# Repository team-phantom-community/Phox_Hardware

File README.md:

# Phoxハードウェア

## 概要
Phoxのハードウェアは完全自作のマイコンボードを中核として様々な小型デバイスを用いている

特にここでは
- 自作ボード回路図
- ハードウェアコンポーネント
- ハードウェア用C++コード

について述べていく

## 必須環境
- Kicad Version 7
- Arduino IDE 2
- ソルダーペースト（ペースト半田）
  - 必須ではないが推奨される
- 半田ごて
- ホットプレート or 温度制限機能付きコンロとフライパン
- 3Dプリンター
- 根気<-最重要

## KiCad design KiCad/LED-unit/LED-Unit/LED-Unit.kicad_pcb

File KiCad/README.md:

# KiCadデータ

## 回路

### メインボード
- CPU : ESP32S3
- Battery : 3.7V 400mAh

- PhoxのメインボードにはESP32S3を用いている
  - ESP32S3は、ビルドインのUSBシリアル変換を用いることでプログラム可能な構成としている
  - なお、書き込みデバイスについてであるが、私の環境ではUSB-Cの半田付けが上手くできなかったため、一般的なUSBケーブルを切って、XHを打ったものを用いている
- カメラモジュールの部分は[ESP32-S3 EYE MB_V2.2](https://dl.espressif.com/dl/schematics/SCH_ESP32-S3-EYE-MB_20211201_V2.2.pdf)を参考に作成してある
- カメラはOV5640を用いる想定になっている
  - OV5640は、OV2640と違いDC1.2Vを必要としないため、個人でESPカメラを自作する際には回路設計の負担が減り、おすすめである
  - OV5640のモジュールは国内であればAmazon、国外であればAliExpressで沢山見つけることができる
- このメインボードでは、実装面積をできるだけ小さくするために4層基板を用いている
- 基板製造はJLCPCBにて行った
  - 個人的にはJLCPCBで作成した基板でパターンがつながっていなかったりしたことがないのでJLCPCBはおすすめである
  - 4層基板であっても5枚で$7(日本円で1,100円)程度製造可能である
- また、部品点数およびサイズが小さかったためリフロー半田付けを行った
  - この際にステンシルがあるとソルダーペーストを載せる時間を大幅に短縮できとても良い
    - が、ステンシルはそれなりに高価なのでお金と時間を考えて相対効果の高いほうを選ぶのが得策だろう
  - リフローの方法についてはGoogleで探せばいろいろ見つかるだろうし、あまり私がやっている方法は推奨されないのでここには記さないこととする
- 完成した基板にUSBをつなげて、Arduino IDE上でCOMポートが認識されていれば問題なし
- IDEでボードの種類をeps32->「ESP32S3 Dev Module」で選択し、[CameraServer](CameraWebServer_Phox_version)を書き込んでシリアルモニタに表示されたhttpアドレスにアクセスし、「Start Stream」をクリックして、カメラの画像が表示されれば基板完成となる

### ドアスイッチモジュール
- PhoxのMBのスイッチング用の磁気スイッチと測距センサを備えたモジュール
- 磁気スイッチにはALPSALPINE社のHGDEST021Bを用いている
  - このMEMSデバイスはALPSALPINE社から直接ご提供いただいた
- 測距センサにはSTMicro社のVL53L0xを用いている
  - このVL53L0xは電源電圧がOV5640と同じ2.8Vであり、非常に使いやすい
- Drawingを見てもらえば分かると思うが、このモジュールはドア近くに付けるという特性上、小型であることが求められるため、幅に関してはPH6ピンコネクタベースと同程度となっている

### LEDユニット
- 郵便受け内が暗くなりがちであることから適切に画像認識を行うためにPhoxにはLEDユニットが搭載されている
- この回路はLEDを並列につなげたものであるため、詳しい説明は省かせていただく

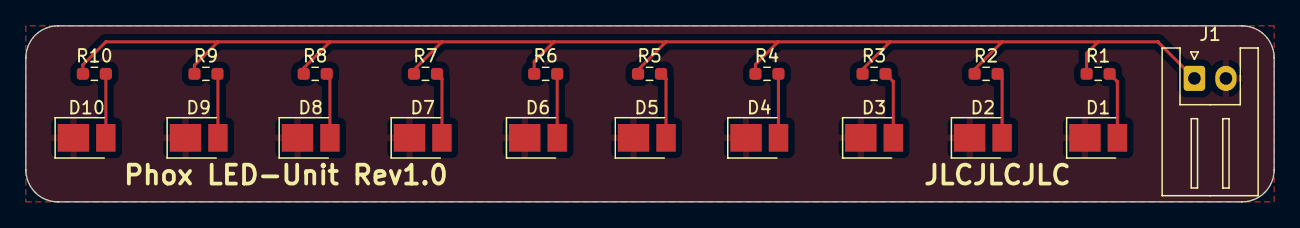
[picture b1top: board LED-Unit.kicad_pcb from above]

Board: 2 copper layers, 99.1 x 14.0 mm, 21 parts (0 on the bottom side), 12 nets.

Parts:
D1, D2, D3, D4, D5, D6, D7, D8, D9, D10: TX1812DXA-F01; LED_PLCC_2835_Handsoldering
J1: Conn_01x02_Socket; JST_XH_S2B-XH-A_1x02_P2.50mm_Horizontal
R1, R2, R3, R4, R5, R6, R7, R8, R9, R10: 100R; R_0603_1608Metric_Pad0.98x0.95mm_HandSolder

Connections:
/GND: D1.1 (K), D2.1 (K), D3.1 (K), D4.1 (K), D5.1 (K), D6.1 (K), D7.1 (K), D8.1 (K), D9.1 (K), D10.1 (K), J1.2
unnamed: D1.2 (A), R1.2
unnamed: D2.2 (A), R2.2
unnamed: D3.2 (A), R3.2
unnamed: D4.2 (A), R4.2
unnamed: D5.2 (A), R5.2
unnamed: D6.2 (A), R6.2
unnamed: D7.2 (A), R7.2
unnamed: D8.2 (A), R8.2
unnamed: D9.2 (A), R9.2
unnamed: D10.2 (A), R10.2
unnamed: J1.1, R1.1, R2.1, R3.1, R4.1, R5.1, R6.1, R7.1, R8.1, R9.1, R10.1

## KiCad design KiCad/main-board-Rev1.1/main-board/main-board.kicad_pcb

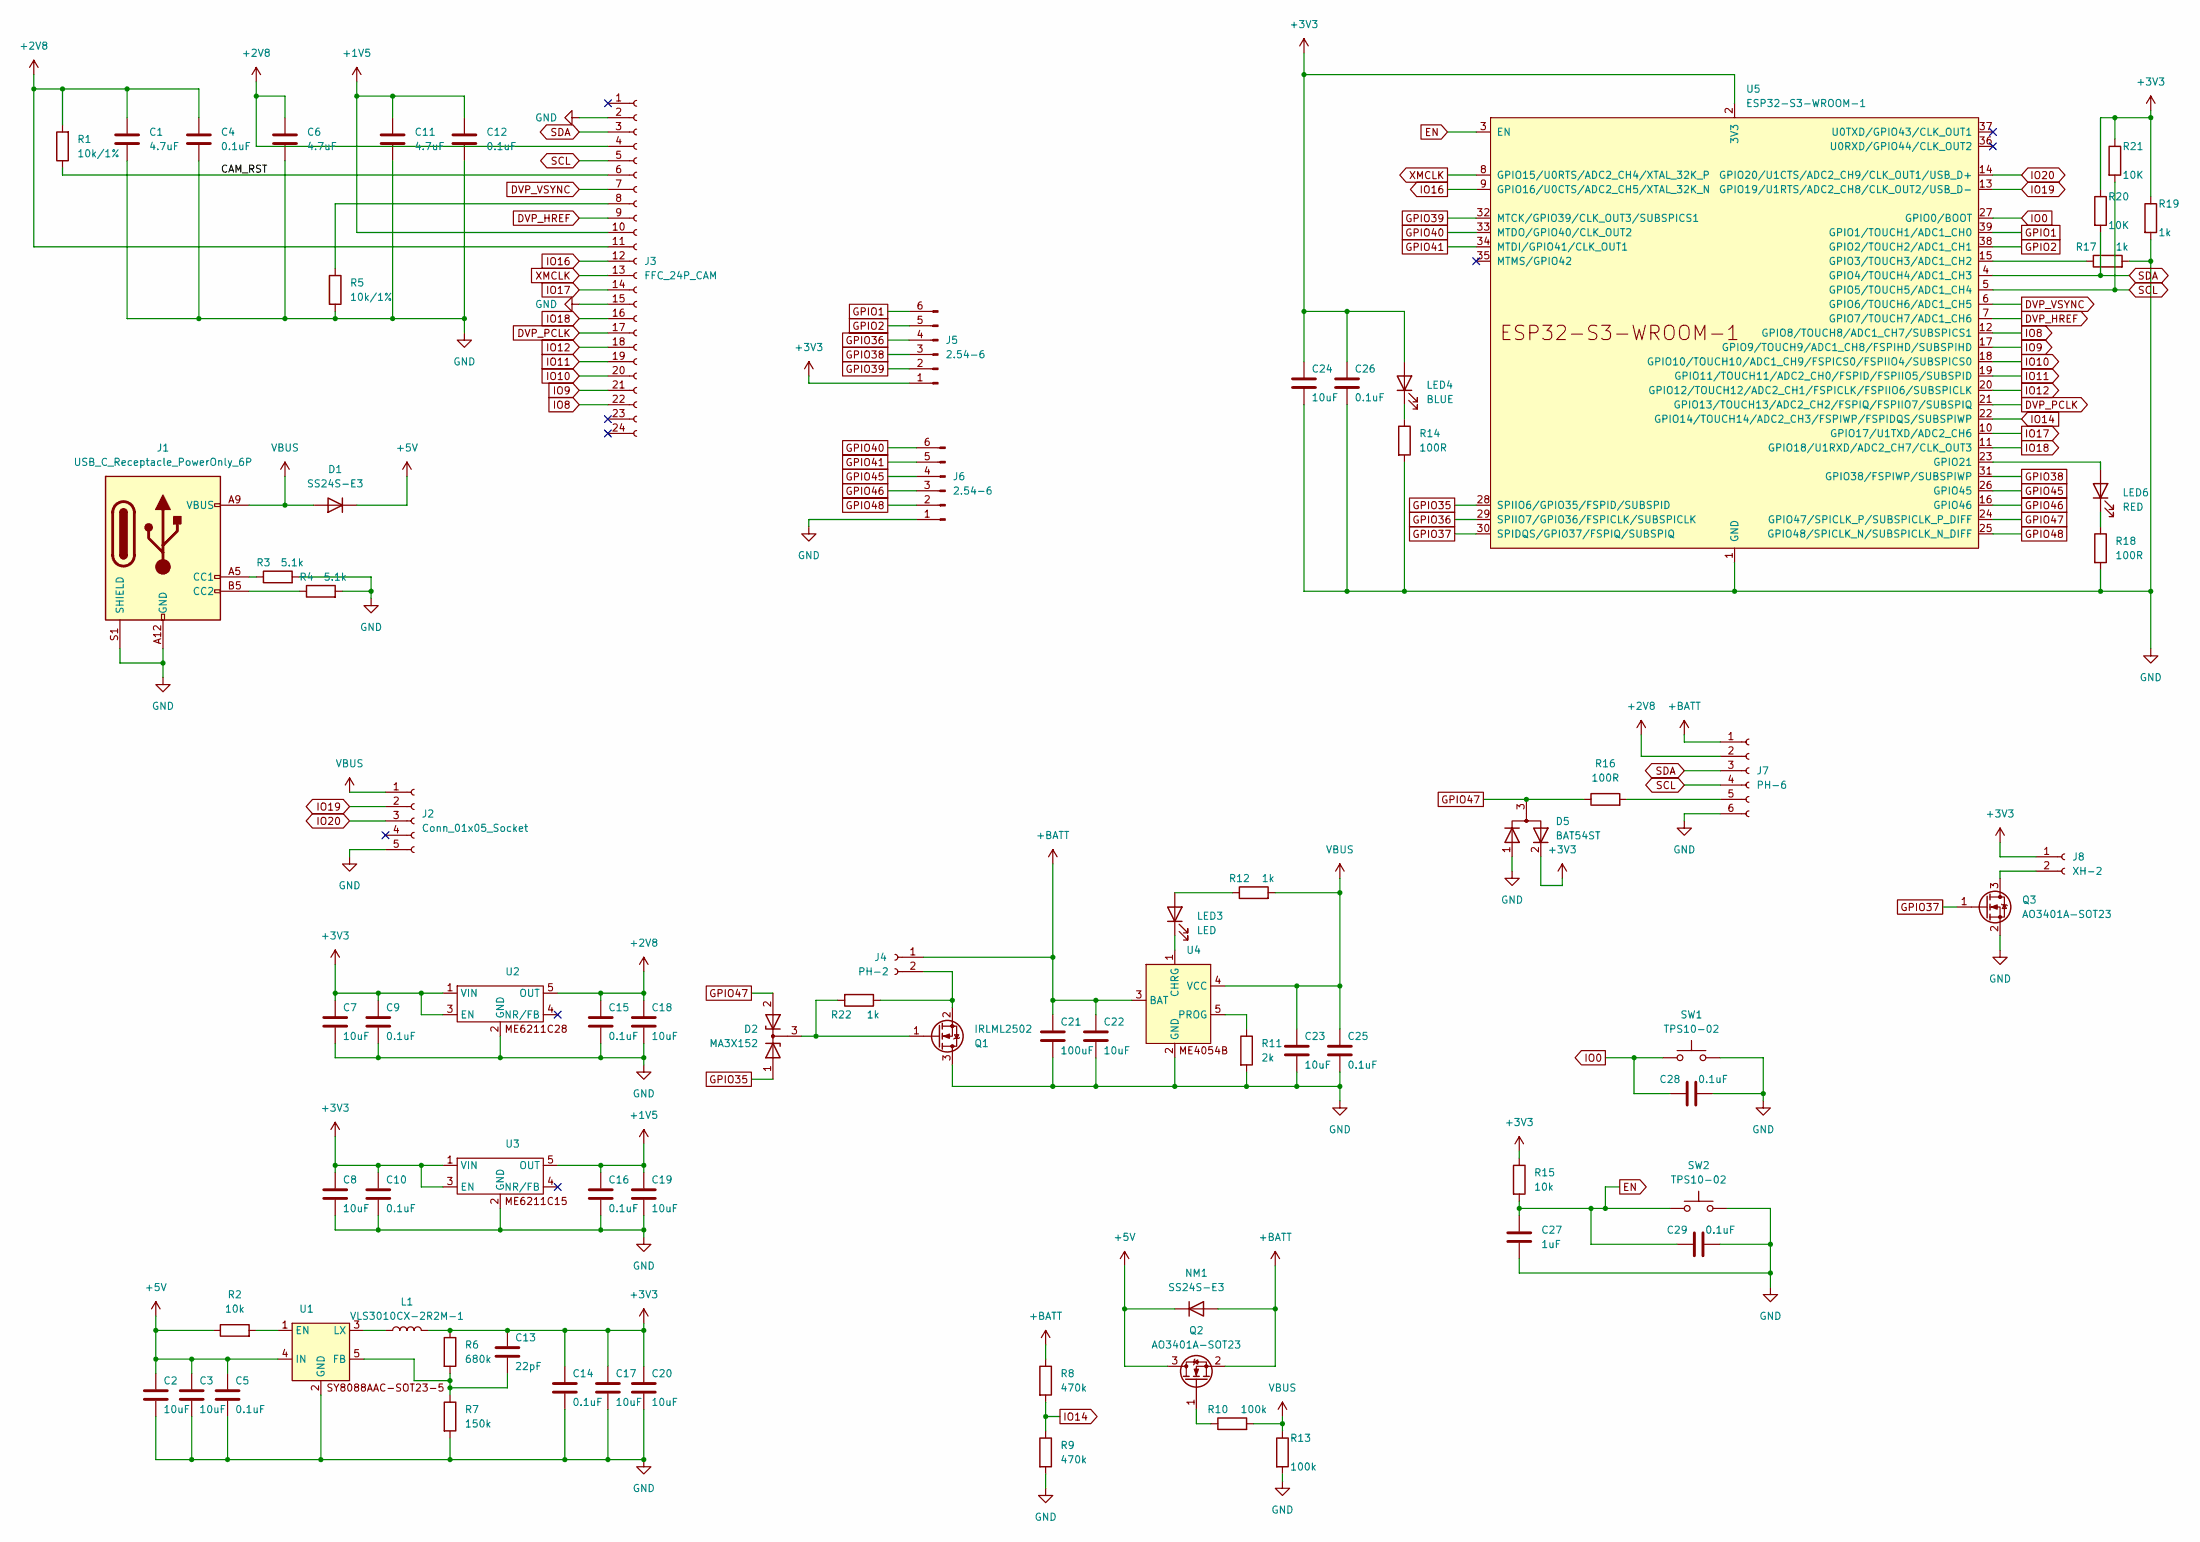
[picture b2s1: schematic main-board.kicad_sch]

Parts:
C1, C6, C11: 4.7uF; CP_EIA-1608-08_AVX-J_Pad1.25x1.05mm_HandSolder
C2, C3, C7, C8, C17, C18, C19, C20, C22, C23: 10uF; CP_EIA-1608-08_AVX-J_Pad1.25x1.05mm_HandSolder
C4, C5, C9, C10, C12, C14, C15, C16, C25, C28, C29: 0.1uF; CP_EIA-1608-08_AVX-J_Pad1.25x1.05mm_HandSolder
C13: 22pF; CP_EIA-1608-08_AVX-J_Pad1.25x1.05mm_HandSolder
C21: 100uF; CP_EIA-1608-08_AVX-J_Pad1.25x1.05mm_HandSolder
C24: 10uF; C_0603_1608Metric_Pad1.08x0.95mm_HandSolder
C26: 0.1uF; C_0603_1608Metric_Pad1.08x0.95mm_HandSolder
C27: 1uF; CP_EIA-1608-08_AVX-J_Pad1.25x1.05mm_HandSolder
D1: SS24S-E3; CR_S-E3&slash_61T_VIS
D2: MA3X152; SOT-23-3
D5: BAT54ST; SOT-23-3
J1: USB_C_Receptacle_PowerOnly_6P; CONN6_UJC-HP-3-SMT-TR_CUD
J2: Conn_01x05_Socket; PinHeader_1x05_P2.54mm_Horizontal
J3: FFC_24P_CAM; FFC24P_cam
J4: PH-2; JST_PH_S2B-PH-K_1x02_P2.00mm_Horizontal
J5, J6: 2.54-6; PinHeader_1x06_P2.54mm_Vertical
J7: PH-6; JST_PH_S6B-PH-K_1x06_P2.00mm_Horizontal
J8: XH-2; JST_XH_S2B-XH-A_1x02_P2.50mm_Horizontal
L1: VLS3010CX-2R2M-1; IND_VLS3010CX-2R2M-1
LED3: LED; LED_0603_1608Metric_Pad1.05x0.95mm_HandSolder
LED4: BLUE; LED_0603_1608Metric_Pad1.05x0.95mm_HandSolder
LED6: RED; LED_0603_1608Metric_Pad1.05x0.95mm_HandSolder
NM1: SS24S-E3; CR_S-E3&slash_61T_VIS
Q1: IRLML2502; SOT-23-3
Q2, Q3: AO3401A-SOT23; SOT-23-3
R1, R5: 10k/1%; R_0603_1608Metric_Pad0.98x0.95mm_HandSolder
R2, R15: 10k; R_0603_1608Metric_Pad0.98x0.95mm_HandSolder
R3, R4: 5.1k; R_0603_1608Metric_Pad0.98x0.95mm_HandSolder
R6: 680k; R_0603_1608Metric_Pad0.98x0.95mm_HandSolder
R7: 150k; R_0603_1608Metric_Pad0.98x0.95mm_HandSolder
R8, R9: 470k; R_0603_1608Metric_Pad0.98x0.95mm_HandSolder
R10, R13: 100k; R_0603_1608Metric_Pad0.98x0.95mm_HandSolder
R11: 2k; R_0603_1608Metric_Pad0.98x0.95mm_HandSolder
R12, R17, R19, R22: 1k; R_0603_1608Metric_Pad0.98x0.95mm_HandSolder
R14, R16, R18: 100R; R_0603_1608Metric_Pad0.98x0.95mm_HandSolder
R20, R21: 10K; R_0603_1608Metric_Pad0.98x0.95mm_HandSolder
SW1, SW2: TPS10-02; SW_pts815
U1, U2, U3, U4: SOT-23-5_HandSoldering
U5: ESP32-S3-WROOM-1

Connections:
+1V5: C11.1, C12.1, C16.1, C19.1, J3.10, U3.5 (OUT)
+2V8: C1.1, C4.1, C6.1, C15.1, C18.1, J3.4, J3.11, J7.2, R1.2, U2.5 (OUT)
+3V3: C7.1, C8.1, C9.1, C10.1, C13.1, C14.1, C17.1, C20.1, C24.1, C26.1, D5.2 (K), J5.1, J8.1, L1.2, LED4.2 (A), R6.1, R15.1, R19.1, R20.1, R21.1, U2.1 (VIN), U2.3 (EN), U3.1 (VIN), U3.3 (EN), U5.2 (3V3)
+5V: C2.1, C3.1, C5.1, D1.1 (K), NM1.1 (K), Q2.3 (D), R2.1, U1.4 (IN)
+BATT: C21.1, C22.1, J4.1, J7.1, NM1.2 (A), Q2.2 (S), R8.1, U4.3 (BAT)
/CAM_RST: J3.6, R1.1
DVP_HREF: J3.9, U5.7 (GPIO7/TOUCH7/ADC1_CH6)
DVP_PCLK: J3.17, U5.21 (GPIO13/TOUCH13/ADC2_CH2/FSPIQ/FSPIIO7/S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)
DVP_VSYNC: J3.7, U5.6 (GPIO6/TOUCH6/ADC1_CH5)
EN: C27.1, C29.1, R15.2, SW2.1, U5.3 (EN)
GND: C1.2, C2.2, C3.2, C4.2, C5.2, C6.2, C7.2, C8.2, C9.2, C10.2, C11.2, C12.2, C14.2, C15.2, C16.2, C17.2, C18.2, C19.2, C20.2, C21.2, C22.2, C23.2, C24.2, C25.2, C26.2, C27.2, C28.2, C29.2, D5.1 (K), J1.A12 (GND), J1.B12 (GND), J1.S1 (SHIELD), J2.5, J3.2, J3.15, J6.1, J7.6, Q1.3 (D), Q3.2 (S), R3.2, R4.2, R5.2, R7.2, R9.2, R11.2, R13.2, R14.2, R17.2, R18.2, R19.2, SW1.2, SW2.2, U1.2 (GND), U2.2 (GND), U3.2 (GND), U4.2 (GND), U5.1 (GND), U5.40 (GND), U5.41 (GND)
GPIO1: J5.6, U5.39 (GPIO1/TOUCH1/ADC1_CH0)
GPIO2: J5.5, U5.38 (GPIO2/TOUCH2/ADC1_CH1)
GPIO35: D2.1 (A), U5.28 (SPIIO6/GPIO35/FSPID/SUBSPID)
GPIO36: J5.4, U5.29 (SPIIO7/GPIO36/FSPICLK/SUBSPICLK)
GPIO37: Q3.1 (G), U5.30 (SPIDQS/GPIO37/FSPIQ/SUBSPIQ)
GPIO38: J5.3, U5.31 (GPIO38/FSPIWP/SUBSPIWP)
GPIO39: J5.2, U5.32 (MTCK/GPIO39/CLK_OUT3/SUBSPICS1)
GPIO40: J6.6, U5.33 (MTDO/GPIO40/CLK_OUT2)
GPIO41: J6.5, U5.34 (MTDI/GPIO41/CLK_OUT1)
GPIO45: J6.4, U5.26 (GPIO45)
GPIO46: J6.3, U5.16 (GPIO46)
GPIO47: D2.2 (A), D5.3 (A), R16.1, U5.24 (GPIO47/SPICLK_P/SUBSPICLK_P_DIFF)
GPIO48: J6.2, U5.25 (GPIO48/SPICLK_N/SUBSPICLK_N_DIFF)
IO0: C28.1, SW1.1, U5.27 (GPIO0/BOOT)
IO8: J3.22, U5.12 (GPIO8/TOUCH8/ADC1_CH7/SUBSPICS1)
IO9: J3.21, U5.17 (GPIO9/TOUCH9/ADC1_CH8/FSPIHD/SUBSPIHD)
IO10: J3.20, U5.18 (GPIO10/TOUCH10/ADC1_CH9/FSPICS0/FSPIIO4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)
IO11: J3.19, U5.19 (GPIO11/TOUCH11/ADC2_CH0/FSPID/FSPIIO5/S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)
IO12: J3.18, U5.20 (GPIO12/TOUCH12/ADC2_CH1/FSPICLK/FSPIIO6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)
IO14: R8.2, R9.1, U5.22 (GPIO14/TOUCH14/ADC2_CH3/FSPIWP/FSPIDQS/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)
IO16: J3.12, U5.9 (GPIO16/U0CTS/ADC2_CH5/XTAL_32K_N)
IO17: J3.14, U5.10 (GPIO17/U1TXD/ADC2_CH6)
IO18: J3.16, U5.11 (GPIO18/U1RXD/ADC2_CH7/CLK_OUT3)
IO19: J2.2, U5.13 (GPIO19/U1RTS/ADC2_CH8/CLK_OUT2/USB_D-)
IO20: J2.3, U5.14 (GPIO20/U1CTS/ADC2_CH9/CLK_OUT1/USB_D+)
unnamed: D2.3 (K), Q1.1 (G), R22.2
unnamed: J1.A5 (CC1), R3.1
unnamed: J1.B5 (CC2), R4.1
unnamed: J3.8, R5.1
unnamed: J4.2, Q1.2 (S), R22.1
unnamed: J7.5, R16.2
unnamed: J8.2, Q3.3 (D)
unnamed: LED3.2 (A), R12.1
unnamed: LED3.1 (K), U4.1 (CHRG)
unnamed: LED4.1 (K), R14.1
unnamed: LED6.2 (A), U5.23 (GPIO21)
unnamed: LED6.1 (K), R18.1
unnamed: Q2.1 (G), R10.1
unnamed: R2.2, U1.1 (EN)
unnamed: C13.2, R6.2, R7.1, U1.5 (FB)
unnamed: L1.1, U1.3 (LX)
unnamed: R11.1, U4.5 (PROG)
unnamed: R17.1, U5.15 (GPIO3/TOUCH3/ADC1_CH2)
SCL: J3.5, J7.4, R21.2, U5.5 (GPIO5/TOUCH5/ADC1_CH4)
SDA: J3.3, J7.3, R20.2, U5.4 (GPIO4/TOUCH4/ADC1_CH3)
VBUS: C23.1, C25.1, D1.2 (A), J1.A9 (VBUS), J1.B9 (VBUS), J2.1, R10.2, R12.2, R13.1, U4.4 (VCC)
XMCLK: J3.13, U5.8 (GPIO15/U0RTS/ADC2_CH4/XTAL_32K_P)

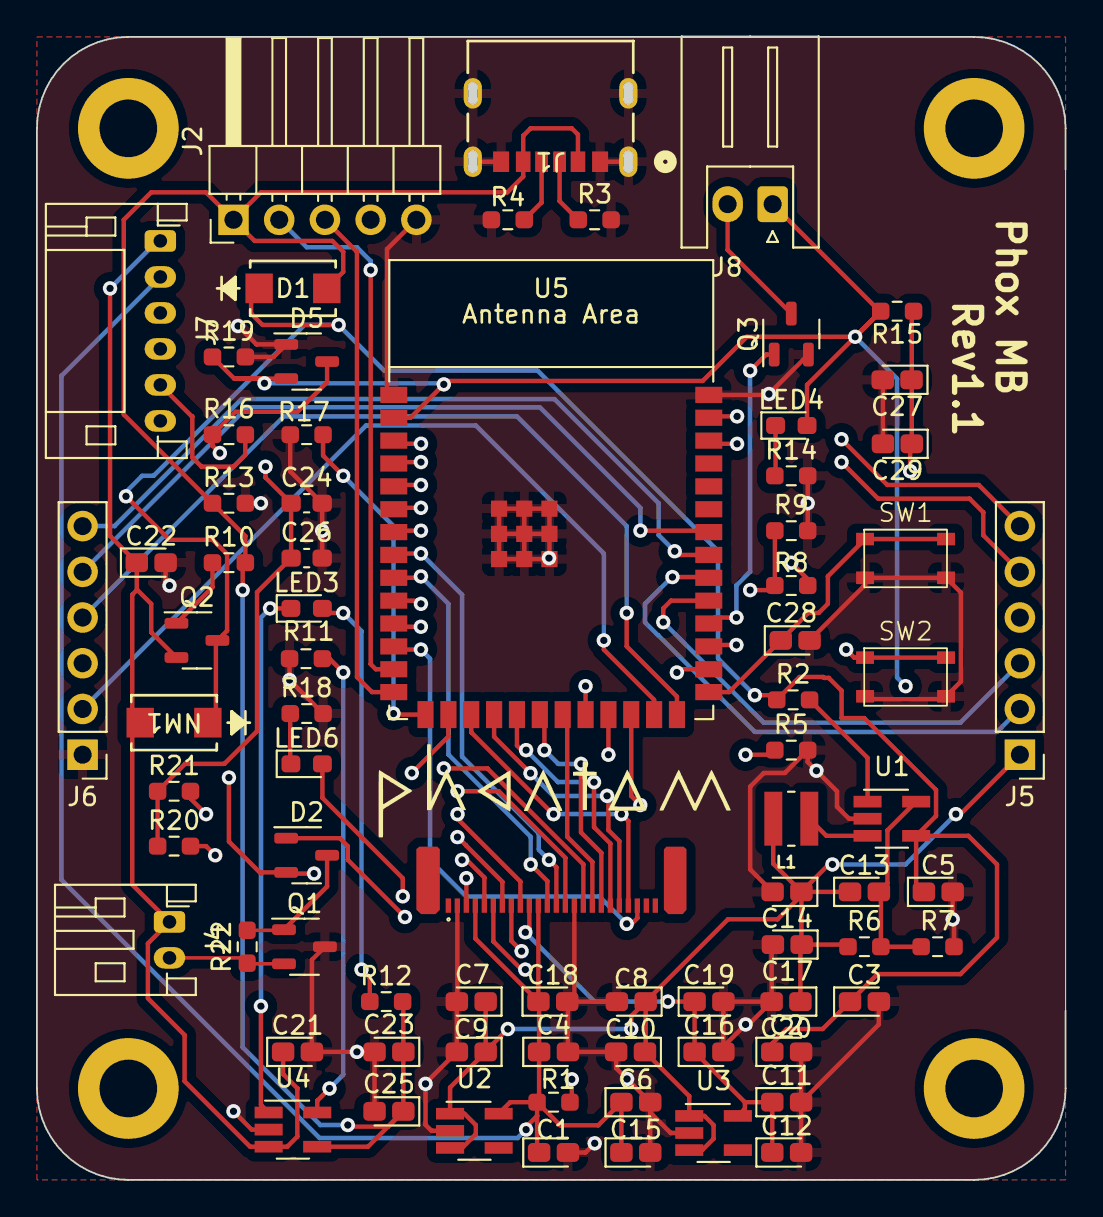
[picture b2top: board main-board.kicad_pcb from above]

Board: 4 copper layers, 56.7 x 63.1 mm, 77 parts (0 on the bottom side), 58 nets.

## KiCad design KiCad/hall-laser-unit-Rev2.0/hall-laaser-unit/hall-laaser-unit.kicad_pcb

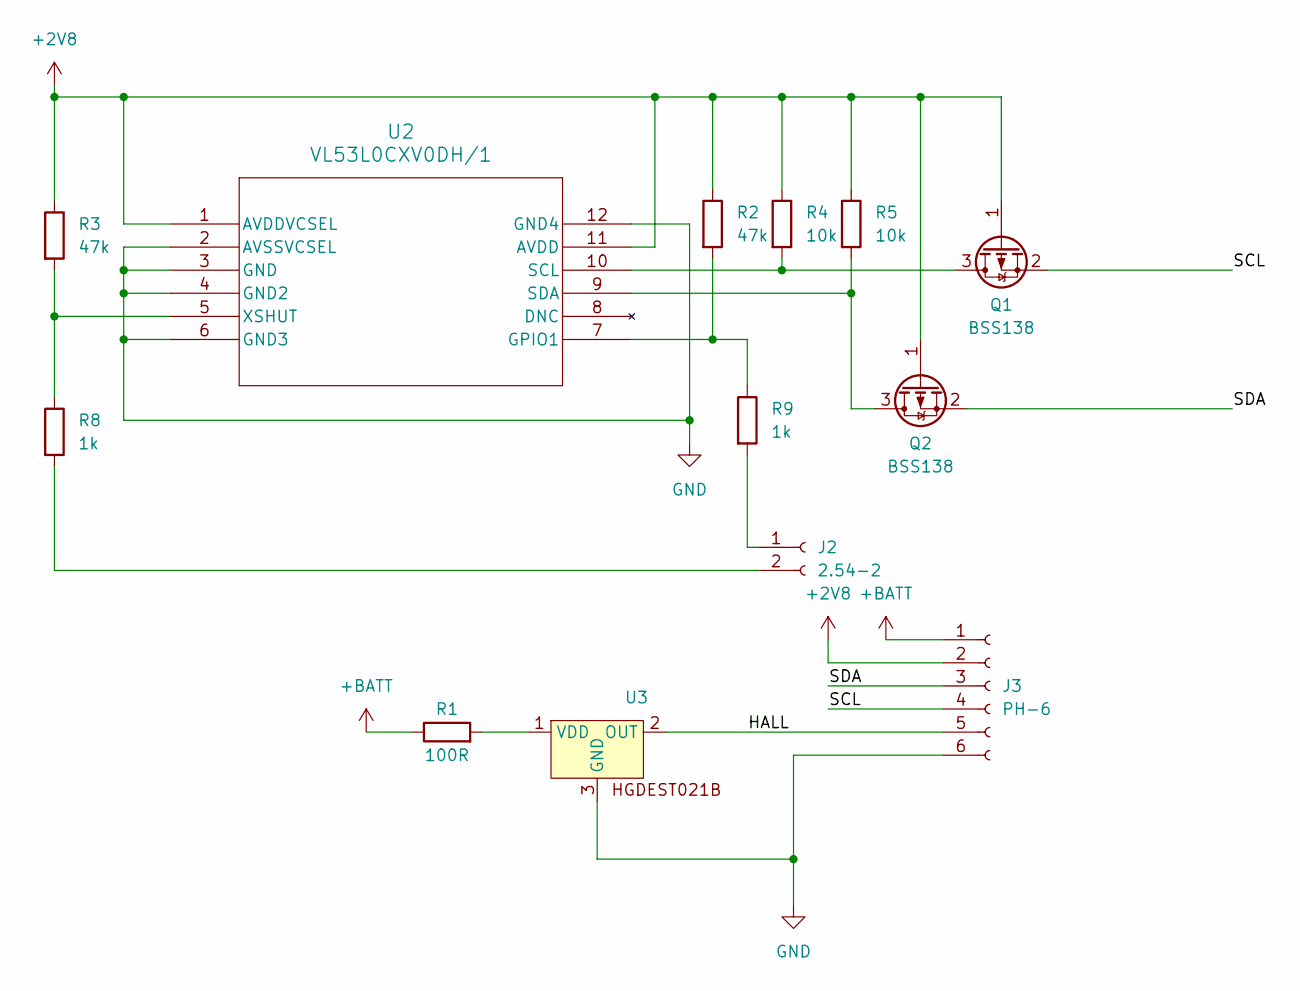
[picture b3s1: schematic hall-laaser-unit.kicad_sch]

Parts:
J2: 2.54-2; PinHeader_1x02_P2.54mm_Vertical
J3: PH-6; JST_PH_S6B-PH-K_1x06_P2.00mm_Horizontal
Q1, Q2: BSS138; SOT-23-3
R1: 100R; R_0603_1608Metric_Pad0.98x0.95mm_HandSolder
R2, R3: 47k; R_0603_1608Metric_Pad0.98x0.95mm_HandSolder
R4, R5: 10k; R_0603_1608Metric_Pad0.98x0.95mm_HandSolder
R8, R9: 1k; R_0603_1608Metric_Pad0.98x0.95mm_HandSolder
U2: VL53L0CXV0DH/1; LGA12_STM-M
U3: SOT-23-3

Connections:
+2V8: J3.2, Q1.1 (G), Q2.1 (G), R2.1, R3.1, R4.1, R5.1, U2.1 (AVDDVCSEL), U2.11 (AVDD)
+BATT: J3.1, R1.1
/HALL: J3.5, U3.2 (OUT)
/SCL: J3.4, Q1.2 (S)
/SDA: J3.3, Q2.2 (S)
GND: J3.6, U2.2 (AVSSVCSEL), U2.3 (GND), U2.4 (GND2), U2.6 (GND3), U2.12 (GND4), U3.3 (GND)
unnamed: J2.1, R9.2
unnamed: J2.2, R8.2
unnamed: Q1.3 (D), R4.2, U2.10 (SCL)
unnamed: Q2.3 (D), R5.2, U2.9 (SDA)
unnamed: R2.2, R9.1, U2.7 (GPIO1)
unnamed: R3.2, R8.1, U2.5 (XSHUT)
unnamed: R1.2, U3.1 (VDD)

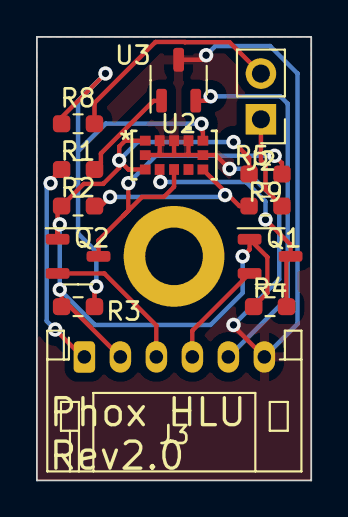
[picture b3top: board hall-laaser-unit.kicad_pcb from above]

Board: 2 copper layers, 15.2 x 24.6 mm, 13 parts (0 on the bottom side), 13 nets.

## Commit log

2024-04-11 add kicad files
2024-04-12 update kicad readme
2024-04-12 create phox code info
